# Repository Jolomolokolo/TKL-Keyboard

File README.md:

# TKL Keyboard – Custom Tenkeyless Mechanical Keyboard with Integrated RP2040

This project is a custom-designed TKL (Tenkeyless) mechanical keyboard with an ISO DE/QWERTZ layout. It features a fully hand-routed PCB with an onboard RP2040 microcontroller, integrated flash memory, reset and boot buttons, and support for hot-swap sockets.

---

## Project Overview

### Keyboard Overview  
This is an overview of the complete TKL keyboard project, including schematic, PCB, and case layout:

---

### Schematic  
The keyboard uses a row-column matrix with diodes to prevent ghosting. The RP2040 is directly mounted on the PCB along with a crystal, power regulation, ESD protection, and SPI flash for firmware storage.

---

### PCB Layout  
The PCB is fully hand-routed and includes:

- RP2040 with external flash memory  
- USB-C port for programming and power  
- Boot and reset buttons  
- Crystal oscillator  
- Fuse for protection  
- Support for hot-swap switch sockets  
- ISO DE/QWERTZ-compliant layout  

---

### Case & Assembly  
The case uses standoffs, heated inserts, and screws to mount the PCB securely. Cutout for USB-C.
Compatible with standard MX keycaps and Cherry stabilizers.

---

## Bill of Materials (BOM)

| Qty | Component              | Value / Description                          | Footprint / Type                      |Price         |
|-----|------------------------|----------------------------------------------|---------------------------------------|--------------|
| 8   | Capacitor              | 100n                                         | C_0402                                |\/            |
| 5   | Capacitor              | 1u                                           | C_0402                                |\/            |
| 2   | Capacitor              | 22p                                          | C_0402                                |\/            |
| 1   | Capacitor              | 10u                                          | C_0603                                |\/            |
| 5   | Resistor               | 5.1k                                         | R_0402                                |\/            |
| 2   | Resistor               | 27k                                          | R_0402                                |\/            |
| 2   | Resistor               | 1k                                           | R_0402                                |\/            |
| 88  | Diodes                 | 1N4148 or equivalent (Ghosting Prevention)   | SOD-123                               |\/            |
| 1   | Microcontroller        | RP2040                                       | QFN-56                                |\/            |
| 1   | Voltage Regulator      | XC6206PxxxMR                                 | SOT-23-3                              |\/            |
| 1   | ESD Protection         | SRV05-4                                      | SOT-23-6                              |\/            |
| 1   | Flash Memory           | W25Q128JVS                                   | SOIC-8                                |\/            |
| 1   | Crystal                | 12MHz / GND24                                | SMD 3225-4Pin                         |\/            |
| 1   | Fuse                   | For USB protection                           | 1206                                  |\/            |
| 2   | Push Button            | Reset / Boot                                 | TL3342                                |$128,97       |
| 88  | Hot-swap Sockets       | MX-compatible                                | CPG151101S11                          |$6,28         | 
| 4   | Stabilizers            | 6.25u / 2.75u / 2u / ISO                     | Cherry MX                             |$11,77        |
| 1   | USB Port               | USB-C 2.0                                    | 16P Receptacle                        |$2,01         |
| 1   | Debug Header           | 4-pin JST                                    | JST-SH 1.0mm                          |\/            |
| 1   | Debug Header           | 5-pin Header                                 | 2.54mm Vertical                       |$3,36         |
| 88  | Switches               | Cherry MX or clone                           | MX-compatible                         |$61,24        |
| 88  | Keycaps                | ISO DE Layout                                | Cherry Profile                        |$16,71        |
| 6   | Standoffs              | 6×6mm M2.5                                   | Female-Male                           |$1,17         |
| 6   | Screws                 | M2.5×6mm                                     | Steel                                 |$1,78         |
| 6   | Heated Inserts         | M2.5×6mm                                     | Brass                                 |$7,93         |
| 1   | USB Cable              | USB-A to USB-C                               | —                                     |-             |
|     |                        |                                              |                                       |Total: $241,22|

* "\/" means: Price is from a package/some parts are bought together and the price is under the arrow pointing down!
* Price is more than $150: I saw a $75 coupon for JLCPCB which would make the price a bit lower and the rest I would pay from my money!
---

## Firmware

The firmware is based on [KMK Firmware](https://github.com/KMKfw/kmk_firmware), a powerful Python-based keyboard firmware running on CircuitPython.

- Full matrix mapping (ISO DE layout)  
- Boot/reset control  
- Flash via USB, no external programmer required

Configuration is managed via `code.py` and `keymap.py`.

- Multi Layer Keyboard will be added!

---

## Future Improvements
 
- Add rotary encoder or OLED display  
- Bluetooth support (via BLE module)  
- Add underglow LED layer

---

## License

This project is open-source under the MIT License.

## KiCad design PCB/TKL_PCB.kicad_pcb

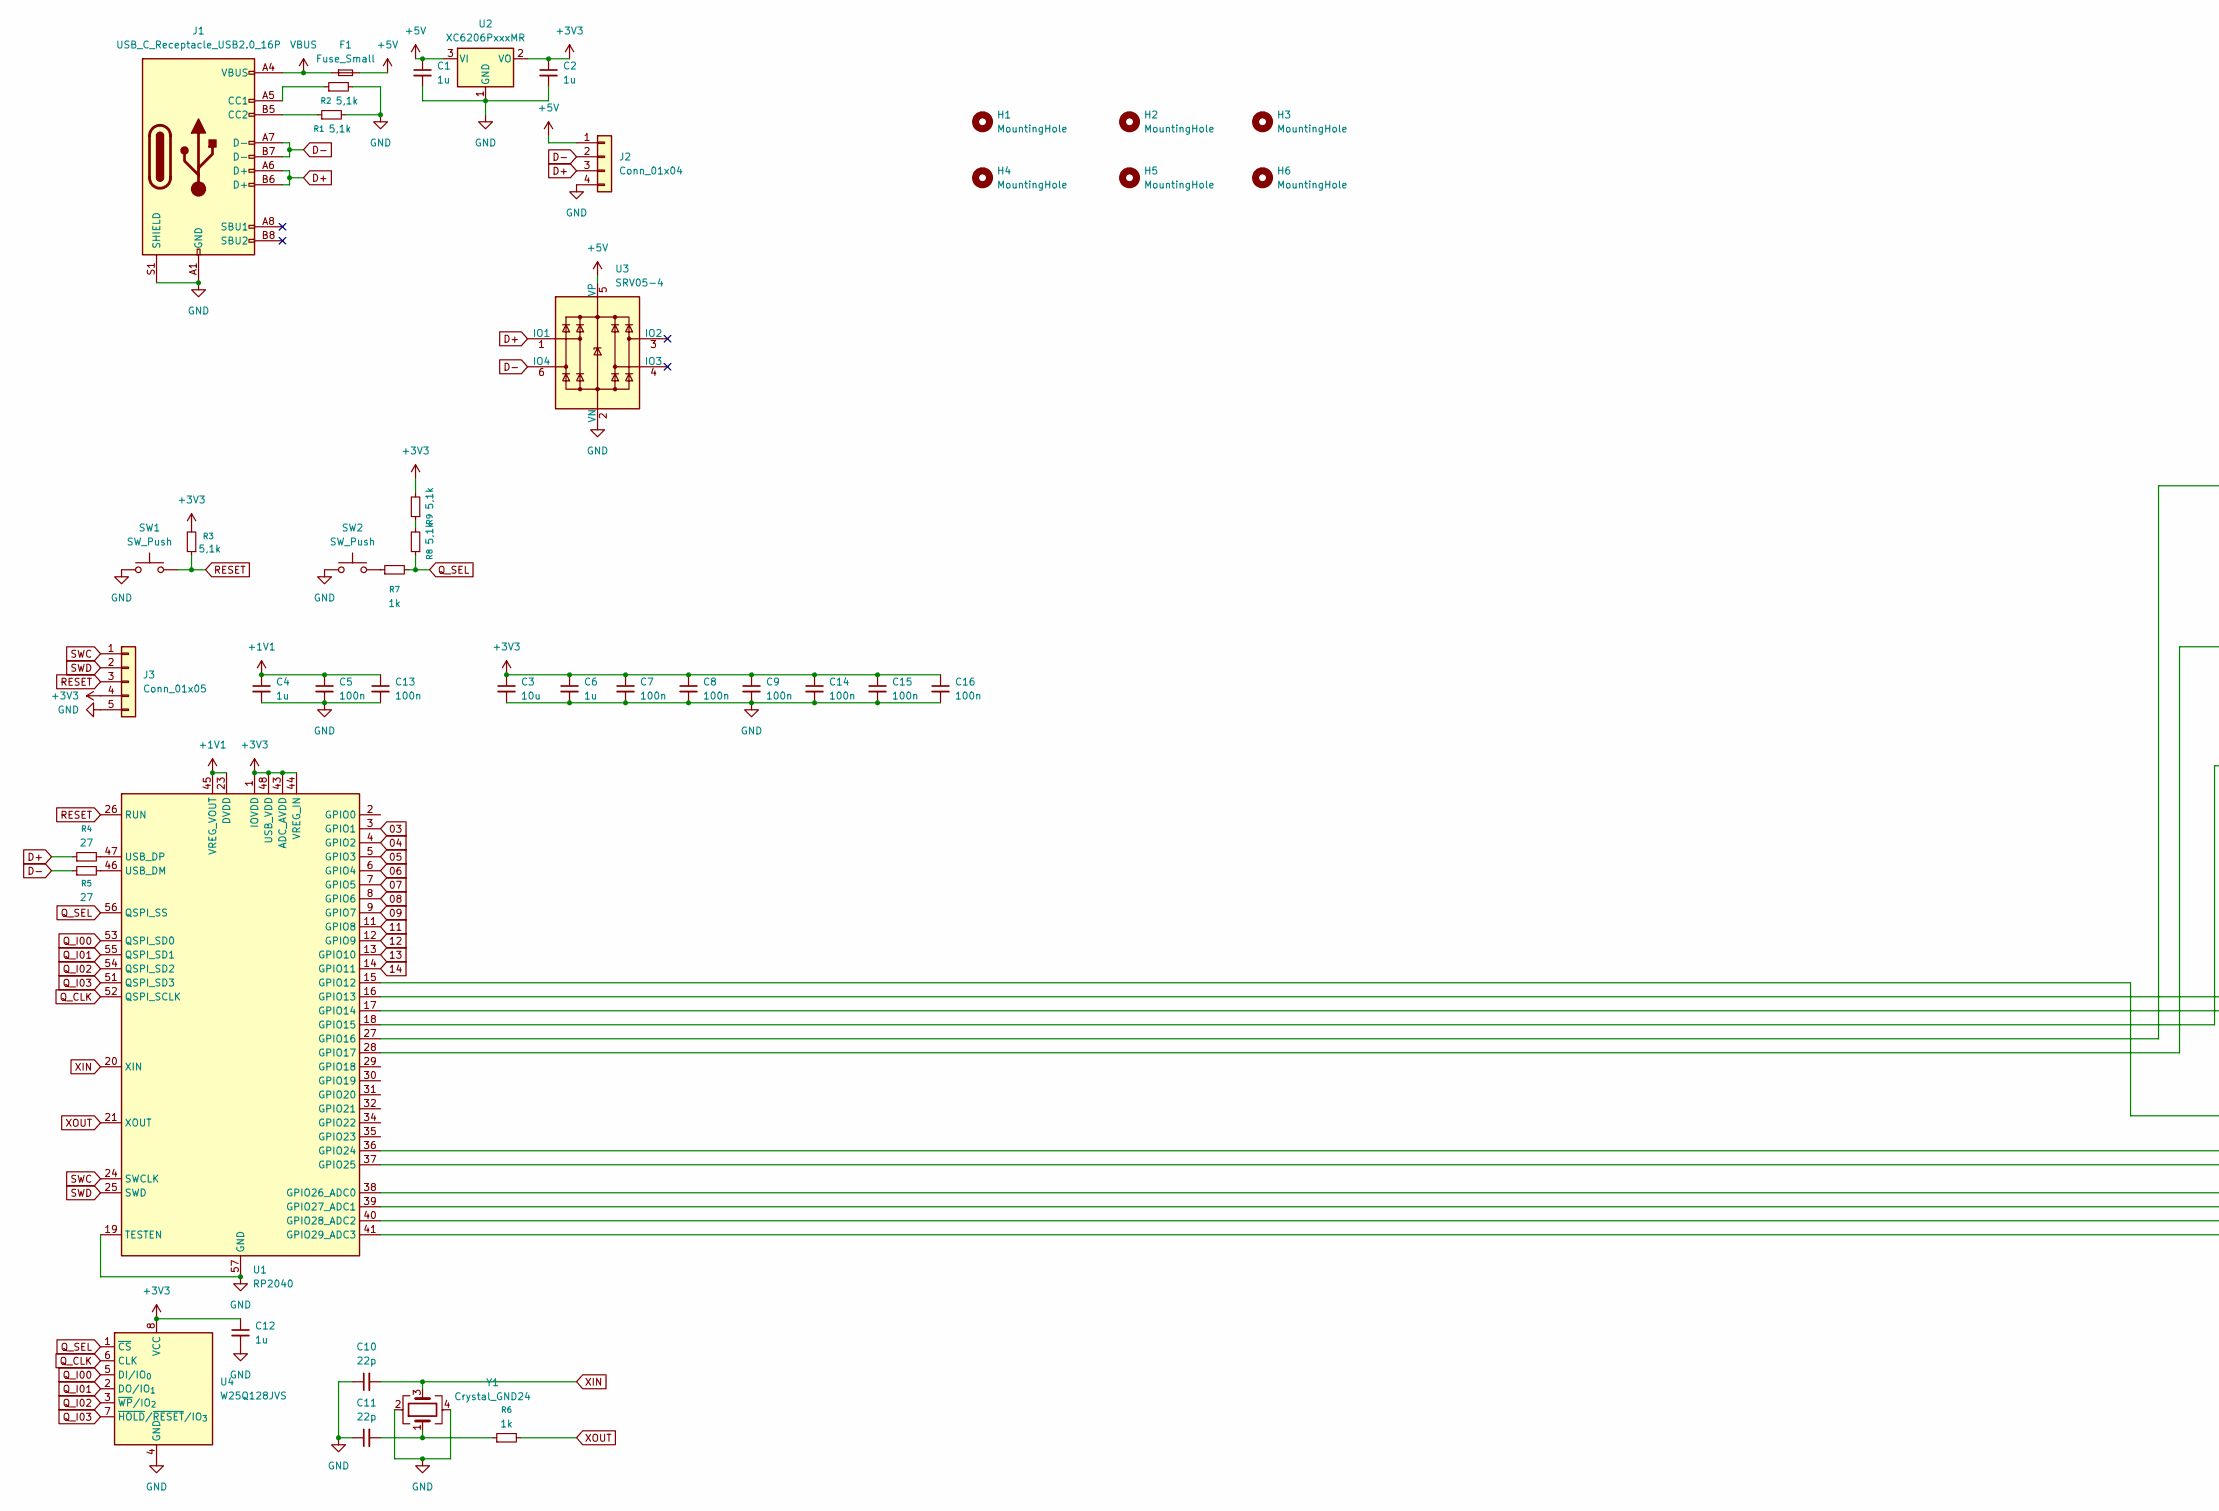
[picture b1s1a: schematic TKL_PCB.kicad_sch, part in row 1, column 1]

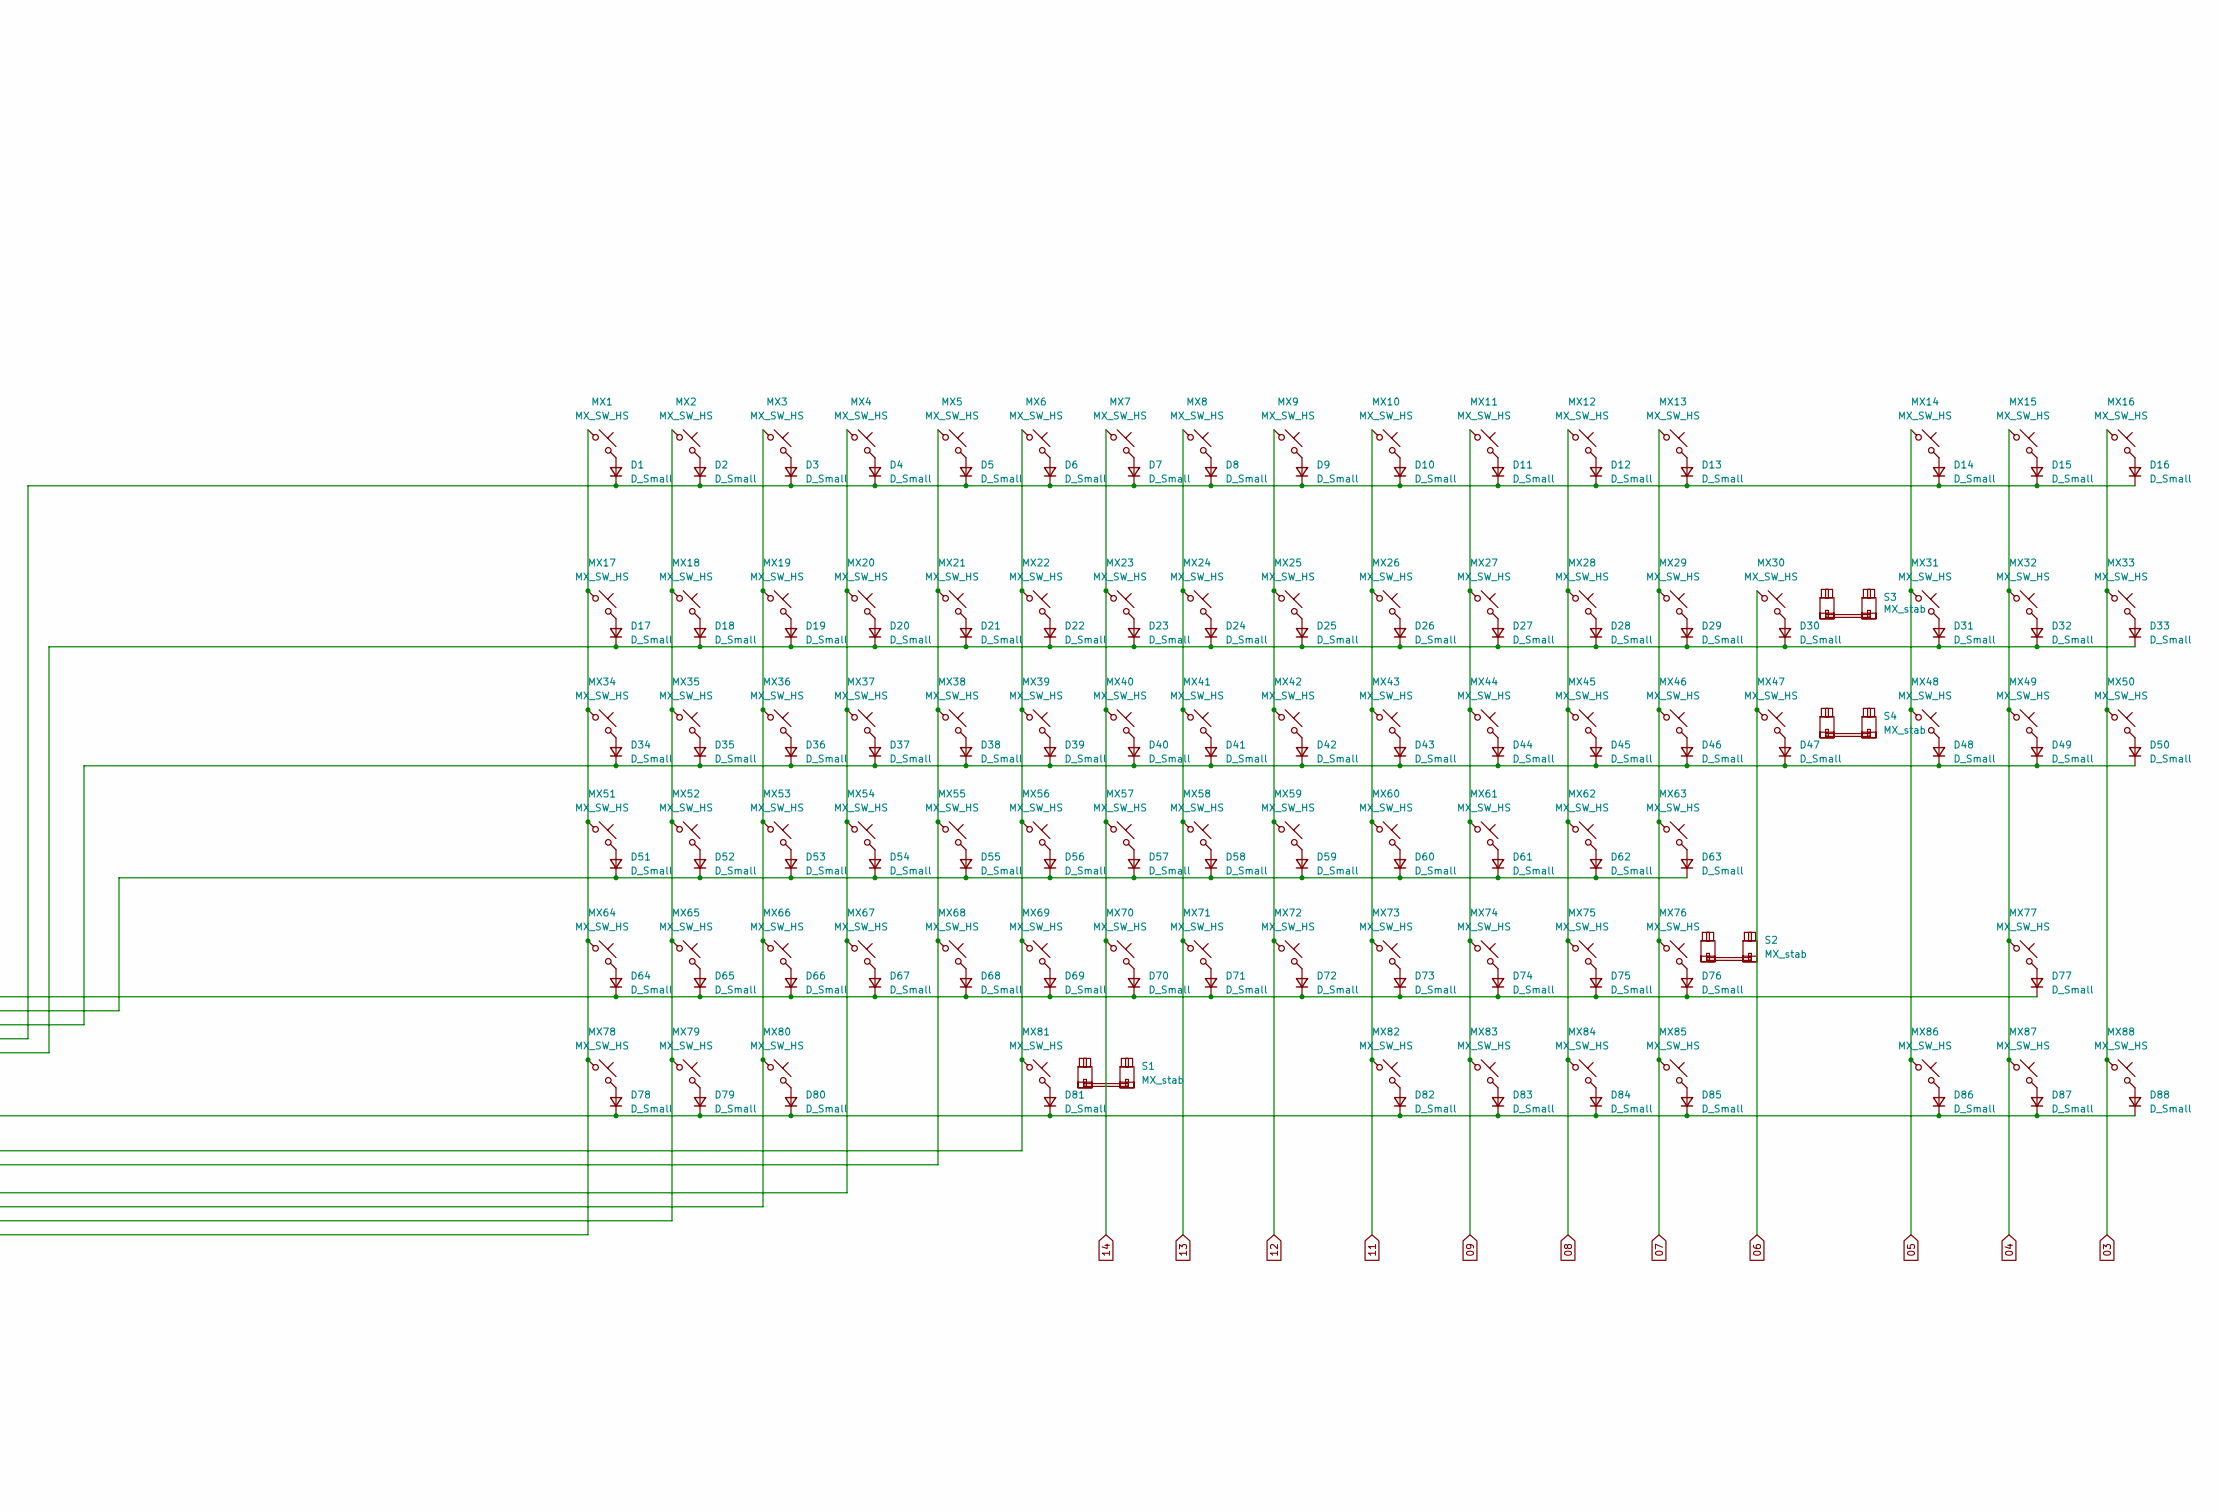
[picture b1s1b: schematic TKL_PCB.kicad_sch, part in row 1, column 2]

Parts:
C1, C2, C4, C6, C12: 1u; C_0402_1005Metric
C3: 10u; C_0603_1608Metric
C5, C7, C8, C9, C13, C14, C15, C16: 100n; C_0402_1005Metric
C10, C11: 22p; C_0402_1005Metric
D1, D2, D3, D4, D5, D6, D7, D8, D9, D10, D11, D12, D13, D14, D15, D16, D17, D18, D19, D20, D21, D22, D23, D24, D25, D26, D27, D28, D29, D30, D31, D32, D33, D34, D35, D36, D37, D38, D39, D40, D41, D42, D43, D44, D45, D46, D47, D48, D49, D50, D51, D52, D53, D54, D55, D56, D57, D58, D59, D60, D61, D62, D63, D64, D65, D66, D67, D68, D69, D70, D71, D72, D73, D74, D75, D76, D77, D78, D79, D80, D81, D82, D83, D84, D85, D86, D87, D88: D_Small; D_SOD-123
F1: Fuse_Small; Fuse_1206_3216Metric
H1, H2, H3, H4, H5, H6: MountingHole; MountingHole_2.5mm
J1: USB_C_Receptacle_USB2.0_16P; USB_C_Receptacle_HRO_TYPE-C-31-M-12
J2: Conn_01x04; JST_SH_SM04B-SRSS-TB_1x04-1MP_P1.00mm_Horizontal
J3: Conn_01x05; PinHeader_1x05_P2.54mm_Vertical
MX1, MX2, MX3, MX4, MX5, MX6, MX7, MX8, MX9, MX10, MX11, MX12, MX13, MX14, MX15, MX16, MX17, MX18, MX19, MX20, MX21, MX22, MX23, MX24, MX25, MX26, MX27, MX28, MX29, MX30, MX31, MX32, MX33, MX35, MX36, MX37, MX38, MX39, MX40, MX41, MX42, MX43, MX44, MX45, MX46, MX47, MX48, MX49, MX50, MX52, MX53, MX54, MX55, MX56, MX57, MX58, MX59, MX60, MX61, MX62, MX63, MX65, MX66, MX67, MX68, MX69, MX70, MX71, MX72, MX73, MX74, MX75, MX76, MX77, MX81, MX86, MX87, MX88: MX_SW_HS; SW_MX_HS_CPG151101S11_1u
MX34: MX_SW_HS; SW_MX_HS_CPG151101S11_1.5u
MX51: MX_SW_HS; SW_MX_HS_CPG151101S11_1.75u_STP_1.25
MX64, MX78, MX79, MX80, MX82, MX83, MX84, MX85: MX_SW_HS; SW_MX_HS_CPG151101S11_1.25u
R1, R2, R3, R8, R9: 5,1k; R_0402_1005Metric
R4, R5: 27; R_0402_1005Metric
R6, R7: 1k; R_0402_1005Metric
S1: MX_stab; STAB_MX_P_6.25u
S2: MX_stab; STAB_MX_P_2.75u
S3: MX_stab; STAB_MX_P_2u
S4: MX_stab; STAB_MX_P_ISO-ROT
SW1, SW2: SW_Push; SW_SPST_TL3342
U1: RP2040; QFN-56-1EP_7x7mm_P0.4mm_EP3.2x3.2mm
U2: XC6206PxxxMR; SOT-23-3
U3: SRV05-4; SOT-23-6-routable
U4: W25Q128JVS; SOIC-8_5.3x5.3mm_P1.27mm
Y1: Crystal_GND24; Crystal_SMD_3225-4Pin_3.2x2.5mm

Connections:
03: MX16.1, MX33.1, MX50.1, MX88.1, U1.3 (GPIO1)
04: MX15.1, MX32.1, MX49.1, MX77.1, MX87.1, U1.4 (GPIO2)
05: MX14.1, MX31.1, MX48.1, MX86.1, U1.5 (GPIO3)
06: MX30.1, MX47.1, U1.6 (GPIO4)
07: MX13.1, MX29.1, MX46.1, MX63.1, MX76.1, MX85.1, U1.7 (GPIO5)
08: MX12.1, MX28.1, MX45.1, MX62.1, MX75.1, MX84.1, U1.8 (GPIO6)
09: MX11.1, MX27.1, MX44.1, MX61.1, MX74.1, MX83.1, U1.9 (GPIO7)
11: MX10.1, MX26.1, MX43.1, MX60.1, MX73.1, MX82.1, U1.11 (GPIO8)
12: MX9.1, MX25.1, MX42.1, MX59.1, MX72.1, U1.12 (GPIO9)
13: MX8.1, MX24.1, MX41.1, MX58.1, MX71.1, U1.13 (GPIO10)
14: MX7.1, MX23.1, MX40.1, MX57.1, MX70.1, U1.14 (GPIO11)
+1V1: C4.1, C5.1, C13.1, U1.23 (DVDD), U1.45 (VREG_VOUT), U1.50 (DVDD)
+3V3: C2.1, C3.1, C6.1, C7.1, C8.1, C9.1, C12.1, C14.1, C15.1, C16.1, J3.4, R3.2, R9.2, U1.1 (IOVDD), U1.10 (IOVDD), U1.22 (IOVDD), U1.33 (IOVDD), U1.42 (IOVDD), U1.43 (ADC_AVDD), U1.44 (VREG_IN), U1.48 (USB_VDD), U1.49 (IOVDD), U2.2 (VO), U4.8 (VCC)
+5V: C1.1, F1.2, J2.1, U2.3 (VI), U3.5 (VP)
D+: J1.A6 (D+), J1.B6 (D+), J2.3, R4.1, U3.1 (IO1)
D-: J1.A7 (D-), J1.B7 (D-), J2.2, R5.1, U3.6 (IO4)
GND: C1.2, C2.2, C3.2, C4.2, C5.2, C6.2, C7.2, C8.2, C9.2, C10.1, C11.1, C12.2, C13.2, C14.2, C15.2, C16.2, J1.A1 (GND), J1.A12 (GND), J1.B1 (GND), J1.B12 (GND), J1.S1 (SHIELD), J2.4, J3.5, R1.2, R2.2, SW1.1, SW2.1, U1.19 (TESTEN), U1.57 (GND), U2.1 (GND), U3.2 (VN), U4.4 (GND), Y1.2, Y1.4
unnamed: C11.2, R6.1, Y1.1
unnamed: D1.2 (A), MX1.2
unnamed: D1.1 (K), D2.1 (K), D3.1 (K), D4.1 (K), D5.1 (K), D6.1 (K), D7.1 (K), D8.1 (K), D9.1 (K), D10.1 (K), D11.1 (K), D12.1 (K), D13.1 (K), D14.1 (K), D15.1 (K), D16.1 (K), U1.27 (GPIO16)
unnamed: D2.2 (A), MX2.2
unnamed: D3.2 (A), MX3.2
unnamed: D4.2 (A), MX4.2
unnamed: D5.2 (A), MX5.2
unnamed: D6.2 (A), MX6.2
unnamed: D7.2 (A), MX7.2
unnamed: D8.2 (A), MX8.2
unnamed: D9.2 (A), MX9.2
unnamed: D10.2 (A), MX10.2
unnamed: D11.2 (A), MX11.2
unnamed: D12.2 (A), MX12.2
unnamed: D13.2 (A), MX13.2
unnamed: D14.2 (A), MX14.2
unnamed: D15.2 (A), MX15.2
unnamed: D16.2 (A), MX16.2
unnamed: D17.2 (A), MX17.2
unnamed: D17.1 (K), D18.1 (K), D19.1 (K), D20.1 (K), D21.1 (K), D22.1 (K), D23.1 (K), D24.1 (K), D25.1 (K), D26.1 (K), D27.1 (K), D28.1 (K), D29.1 (K), D30.1 (K), D31.1 (K), D32.1 (K), D33.1 (K), U1.28 (GPIO17)
unnamed: D18.2 (A), MX18.2
unnamed: D19.2 (A), MX19.2
unnamed: D20.2 (A), MX20.2
unnamed: D21.2 (A), MX21.2
unnamed: D22.2 (A), MX22.2
unnamed: D23.2 (A), MX23.2
unnamed: D24.2 (A), MX24.2
unnamed: D25.2 (A), MX25.2
unnamed: D26.2 (A), MX26.2
unnamed: D27.2 (A), MX27.2
unnamed: D28.2 (A), MX28.2
unnamed: D29.2 (A), MX29.2
unnamed: D30.2 (A), MX30.2
unnamed: D31.2 (A), MX31.2
unnamed: D32.2 (A), MX32.2
unnamed: D33.2 (A), MX33.2
unnamed: D34.2 (A), MX34.2
unnamed: D34.1 (K), D35.1 (K), D36.1 (K), D37.1 (K), D38.1 (K), D39.1 (K), D40.1 (K), D41.1 (K), D42.1 (K), D43.1 (K), D44.1 (K), D45.1 (K), D46.1 (K), D47.1 (K), D48.1 (K), D49.1 (K), D50.1 (K), U1.18 (GPIO15)
unnamed: D35.2 (A), MX35.2
unnamed: D36.2 (A), MX36.2
unnamed: D37.2 (A), MX37.2
unnamed: D38.2 (A), MX38.2
unnamed: D39.2 (A), MX39.2
unnamed: D40.2 (A), MX40.2
unnamed: D41.2 (A), MX41.2
unnamed: D42.2 (A), MX42.2
unnamed: D43.2 (A), MX43.2
unnamed: D44.2 (A), MX44.2
unnamed: D45.2 (A), MX45.2
unnamed: D46.2 (A), MX46.2
unnamed: D47.2 (A), MX47.2
unnamed: D48.2 (A), MX48.2
unnamed: D49.2 (A), MX49.2
unnamed: D50.2 (A), MX50.2
unnamed: D51.2 (A), MX51.2
unnamed: D51.1 (K), D52.1 (K), D53.1 (K), D54.1 (K), D55.1 (K), D56.1 (K), D57.1 (K), D58.1 (K), D59.1 (K), D60.1 (K), D61.1 (K), D62.1 (K), D63.1 (K), U1.17 (GPIO14)
unnamed: D52.2 (A), MX52.2
unnamed: D53.2 (A), MX53.2
unnamed: D54.2 (A), MX54.2
unnamed: D55.2 (A), MX55.2
unnamed: D56.2 (A), MX56.2
unnamed: D57.2 (A), MX57.2
unnamed: D58.2 (A), MX58.2
unnamed: D59.2 (A), MX59.2
unnamed: D60.2 (A), MX60.2
unnamed: D61.2 (A), MX61.2
unnamed: D62.2 (A), MX62.2
unnamed: D63.2 (A), MX63.2
unnamed: D64.2 (A), MX64.2
unnamed: D64.1 (K), D65.1 (K), D66.1 (K), D67.1 (K), D68.1 (K), D69.1 (K), D70.1 (K), D71.1 (K), D72.1 (K), D73.1 (K), D74.1 (K), D75.1 (K), D76.1 (K), D77.1 (K), U1.16 (GPIO13)
unnamed: D65.2 (A), MX65.2
unnamed: D66.2 (A), MX66.2
unnamed: D67.2 (A), MX67.2
unnamed: D68.2 (A), MX68.2
unnamed: D69.2 (A), MX69.2
unnamed: D70.2 (A), MX70.2
unnamed: D71.2 (A), MX71.2
unnamed: D72.2 (A), MX72.2
unnamed: D73.2 (A), MX73.2
unnamed: D74.2 (A), MX74.2
unnamed: D75.2 (A), MX75.2
unnamed: D76.2 (A), MX76.2
unnamed: D77.2 (A), MX77.2
unnamed: D78.2 (A), MX78.2
unnamed: D78.1 (K), D79.1 (K), D80.1 (K), D81.1 (K), D82.1 (K), D83.1 (K), D84.1 (K), D85.1 (K), D86.1 (K), D87.1 (K), D88.1 (K), U1.15 (GPIO12)
unnamed: D79.2 (A), MX79.2
unnamed: D80.2 (A), MX80.2
unnamed: D81.2 (A), MX81.2
unnamed: D82.2 (A), MX82.2
unnamed: D83.2 (A), MX83.2
unnamed: D84.2 (A), MX84.2
unnamed: D85.2 (A), MX85.2
unnamed: D86.2 (A), MX86.2
unnamed: D87.2 (A), MX87.2
unnamed: D88.2 (A), MX88.2
unnamed: J1.A5 (CC1), R2.1
unnamed: J1.B5 (CC2), R1.1
unnamed: R7.1, SW2.2
unnamed: R8.2, R9.1
unnamed: MX6.1, MX22.1, MX39.1, MX56.1, MX69.1, MX81.1, U1.36 (GPIO24)
unnamed: MX5.1, MX21.1, MX38.1, MX55.1, MX68.1, U1.37 (GPIO25)
unnamed: MX4.1, MX20.1, MX37.1, MX54.1, MX67.1, U1.38 (GPIO26_ADC0)
unnamed: MX3.1, MX19.1, MX36.1, MX53.1, MX66.1, MX80.1, U1.39 (GPIO27_ADC1)
unnamed: MX2.1, MX18.1, MX35.1, MX52.1, MX65.1, MX79.1, U1.40 (GPIO28_ADC2)
unnamed: MX1.1, MX17.1, MX34.1, MX51.1, MX64.1, MX78.1, U1.41 (GPIO29_ADC3)
unnamed: R5.2, U1.46 (USB_DM)
unnamed: R4.2, U1.47 (USB_DP)
Q_CLK: U1.52 (QSPI_SCLK), U4.6 (CLK)
Q_I00: U1.53 (QSPI_SD0), U4.5 (DI/IO_{0})
Q_I01: U1.55 (QSPI_SD1), U4.2 (DO/IO_{1})
Q_I02: U1.54 (QSPI_SD2), U4.3 (~WP/IO_{2})
Q_I03: U1.51 (QSPI_SD3), U4.7 (~HOLD/~RESET/IO_{3})
Q_SEL: R7.2, R8.1, U1.56 (QSPI_SS), U4.1 (~CS)
RESET: J3.3, R3.1, SW1.2, U1.26 (RUN)
SWC: J3.1, U1.24 (SWCLK)
SWD: J3.2, U1.25 (SWD)
VBUS: F1.1, J1.A4 (VBUS), J1.A9 (VBUS), J1.B4 (VBUS), J1.B9 (VBUS)
XIN: C10.2, U1.20 (XIN), Y1.3
XOUT: R6.2, U1.21 (XOUT)

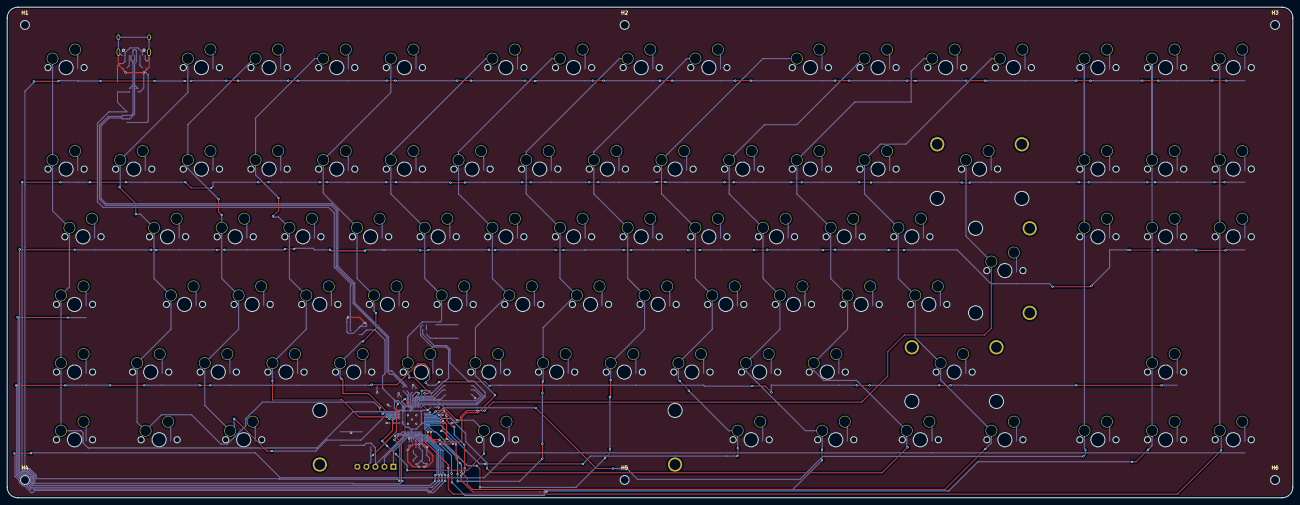
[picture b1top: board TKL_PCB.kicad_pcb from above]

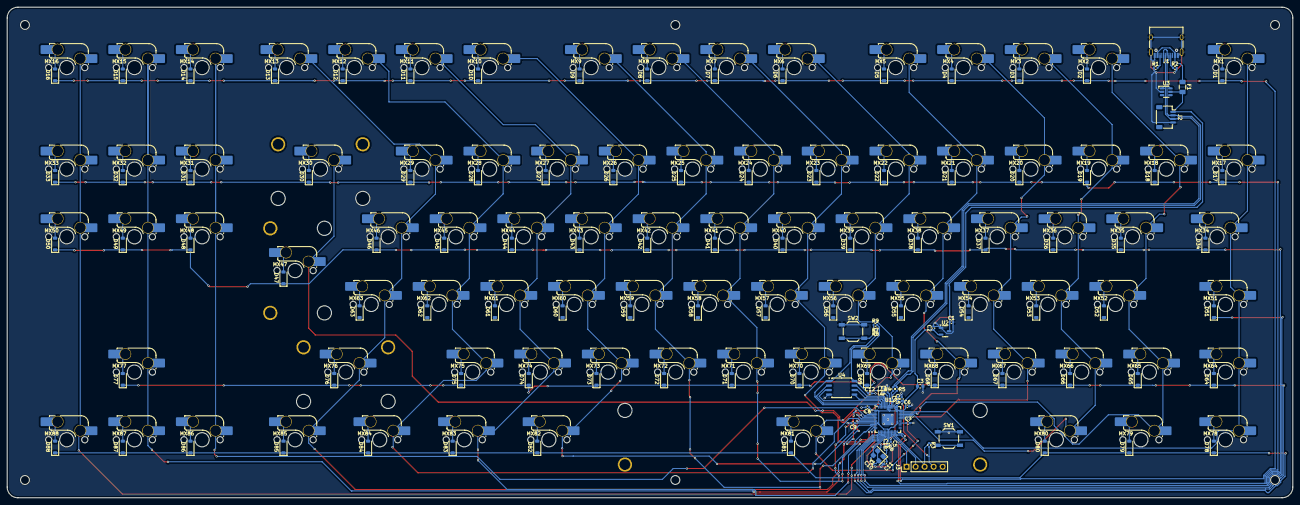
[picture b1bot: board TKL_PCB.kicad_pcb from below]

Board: 2 copper layers, 361.9 x 138.1 mm, 222 parts (212 on the bottom side), 136 nets.

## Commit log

2025-07-02 Add initial firmware and expand project documentation
    Added boot.py, code.py, and keymap.py to provide initial CircuitPython/KMK firmware for the custom TKL keyboard. Updated README.md with detailed project overview, schematic, PCB layout, case assembly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
2025-07-05 Added prices to BOM
